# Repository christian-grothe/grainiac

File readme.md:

# Grainiac

Grainiac is a granular sampler. It currently runs as a vst3 plugin, standlone with a tui and a vst3 plugin with a tui style interface which is currently experimental and under development.

## Project Structure

| Crate                 | Description                                               |
| --------------------- | --------------------------------------------------------- |
| `grainiac_core`       | Core audio DSP engine (no UI dependencies)                |
| `grainiac_tui`        | Standalone JACK client with Ratatui TUI                   |
| `grainiac_plugin_tui` | VST3/CLAP plugin with Ratatui TUI editor _(experimental)_ |
| `grainiac_plugin_gui` | Vizia-based GUI plugin                                    |
| `midi_ctrl`           | PlatformIO firmware for Teensy 4.0 MIDI controller        |

## Config

You need a `config.json` file under `~/.config/grainiac/` with the following schema:

```json
{
  "presets": [
    {
      "gain": [0.5, 0.5, 0.5, 0.5],
      "loop_start": [0.25, 0.25, 0.25, 0.25],
      "loop_length": [0.5, 0.5, 0.5, 0.5],
      "density": [0.5, 0.5, 0.5, 0.5],
      "grain_length": [0.5, 0.5, 0.5, 0.5],
      "play_speed": [1.0, 1.0, 1.0, 1.0],
      "spray": [0.1, 0.1, 0.1, 0.1],
      "pan": [0.0, 0.0, 0.0, 0.0],
      "spread": [1.0, 1.0, 1.0, 1.0],
      "attack": [0.25, 0.25, 0.25, 0.25],
      "release": [0.25, 0.25, 0.25, 0.25],
      "pitch": [1, 1, 1, 1],
      "play_dir": [0, 0, 0, 0],
      "grain_dir": [0, 0, 0, 0],
      "mode": [0, 0, 0, 0],
      "name": "preset_1",
      "char": "1"
    }
  ],
  "mapping": {
    "loop_start": 40,
    "loop_length": 41,
    "density": 42,
    "grain_length": 43,
    "play_speed": 44,
    "spray": 45,
    "pan": 46,
    "spread": 47,
    "attack": 48,
    "release": 49,
    "pitch": 50,
    "gain": 51,
    "record": 52,
    "hold": 53,
    "play_dir": 54,
    "grain_dir": 55,
    "mode": 56
  }
}
```

The arrays under presets represent tracks A to D. The `char` field is the key to press to load the preset. The `name` field is currently unused.

The `mapping` section maps MIDI CC numbers to parameters. Each track corresponds to a MIDI channel (channel 1 = track A, channel 2 = track B, etc.).

To save and load audio files, manually create the folder `~/.local/share/grainiac/`.

## Key Mappings

| Key    | Function    |
| ------ | ----------- |
| `m`    | change mode |
| `0..9` | load / save |
| `n`    | switch view |
| `esc`  | close       |

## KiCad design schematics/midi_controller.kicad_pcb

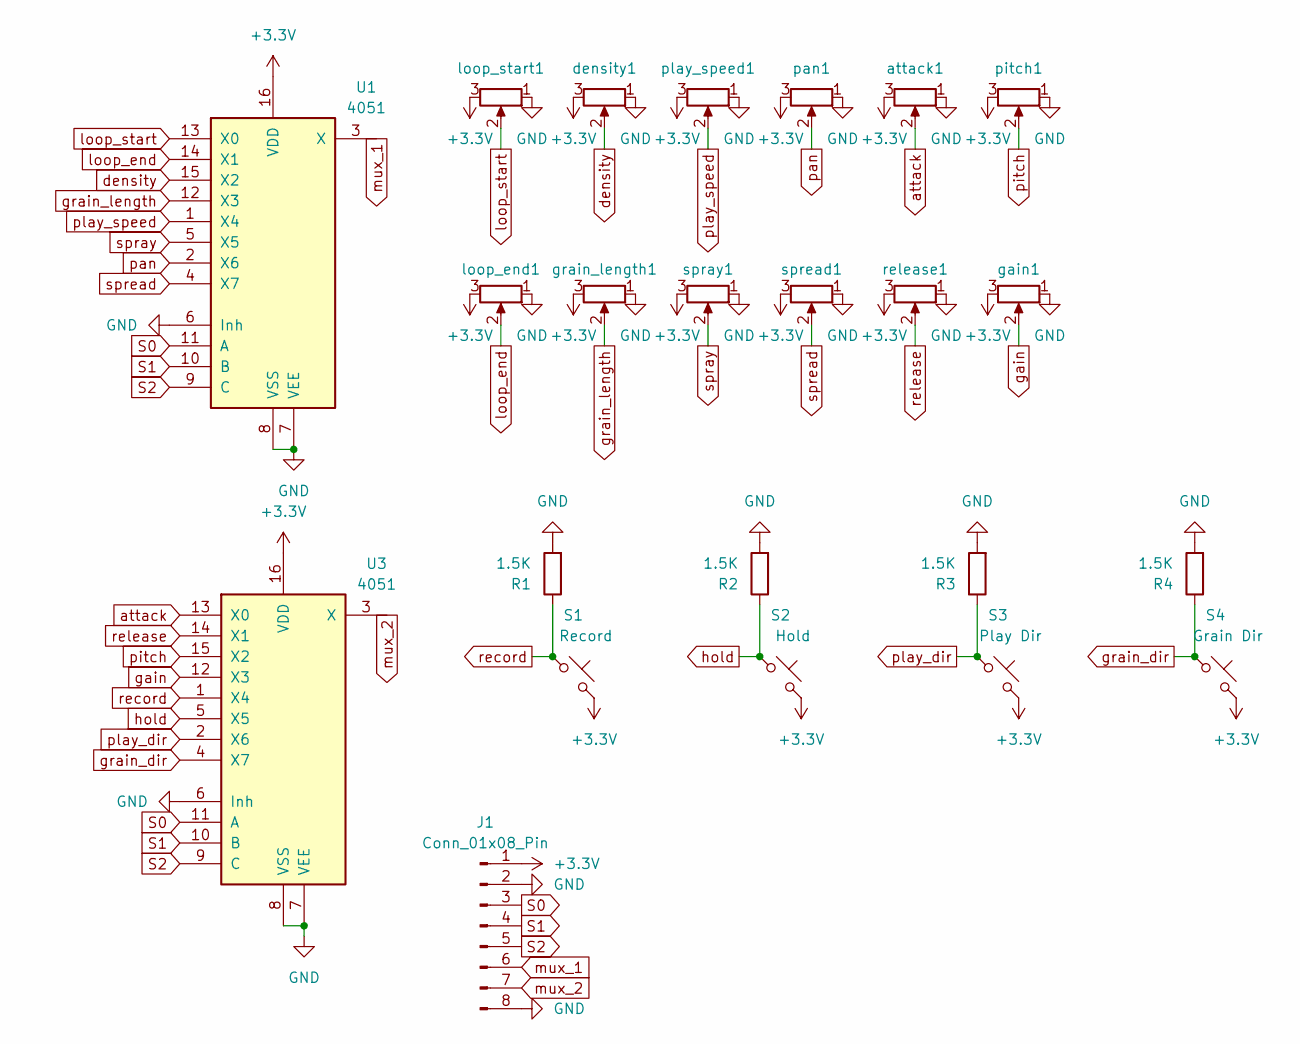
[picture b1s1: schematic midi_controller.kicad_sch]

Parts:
J1: Conn_01x08_Pin; IDC-Header_2x04_P2.54mm_Vertical
R1, R2, R3, R4: 1.5K; R_Axial_DIN0204_L3.6mm_D1.6mm_P5.08mm_Horizontal
S1: Record; SW_Cherry_MX_1.00u_PCB
S2: Hold; SW_Cherry_MX_1.00u_PCB
S3: Play Dir; SW_Cherry_MX_1.00u_PCB
S4: Grain Dir; SW_Cherry_MX_1.00u_PCB
U1, U3: 4051; DIP-16_W7.62mm_Socket
attack1: Potentiometer_TT_P0915N
density1: Potentiometer_TT_P0915N
gain1: Potentiometer_TT_P0915N
grain_length1: Potentiometer_TT_P0915N
loop_end1: Potentiometer_TT_P0915N
loop_start1: Potentiometer_TT_P0915N
pan1: Potentiometer_TT_P0915N
pitch1: Potentiometer_TT_P0915N
play_speed1: Potentiometer_TT_P0915N
release1: Potentiometer_TT_P0915N
spray1: Potentiometer_TT_P0915N
spread1: Potentiometer_TT_P0915N

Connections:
+3.3V: J1.1, S1.2, S2.2, S3.2, S4.2, U1.16 (VDD), U3.16 (VDD), attack1.3, density1.3, gain1.3, grain_length1.3, loop_end1.3, loop_start1.3, pan1.3, pitch1.3, play_speed1.3, release1.3, spray1.3, spread1.3
GND: J1.2, J1.8, R1.2, R2.2, R3.2, R4.2, U1.6 (Inh), U1.7 (VEE), U1.8 (VSS), U3.6 (Inh), U3.7 (VEE), U3.8 (VSS), attack1.1, density1.1, gain1.1, grain_length1.1, loop_end1.1, loop_start1.1, pan1.1, pitch1.1, play_speed1.1, release1.1, spray1.1, spread1.1
S0: J1.3, U1.11 (A), U3.11 (A)
S1: J1.4, U1.10 (B), U3.10 (B)
S2: J1.5, U1.9 (C), U3.9 (C)
attack: U3.13 (X0), attack1.2
density: U1.15 (X2), density1.2
gain: U3.12 (X3), gain1.2
grain_dir: R4.1, S4.1, U3.4 (X7)
grain_length: U1.12 (X3), grain_length1.2
hold: R2.1, S2.1, U3.5 (X5)
loop_end: U1.14 (X1), loop_end1.2
loop_start: U1.13 (X0), loop_start1.2
mux_1: J1.6, U1.3 (X)
mux_2: J1.7, U3.3 (X)
pan: U1.2 (X6), pan1.2
pitch: U3.15 (X2), pitch1.2
play_dir: R3.1, S3.1, U3.2 (X6)
play_speed: U1.1 (X4), play_speed1.2
record: R1.1, S1.1, U3.1 (X4)
release: U3.14 (X1), release1.2
spray: U1.5 (X5), spray1.2
spread: U1.4 (X7), spread1.2

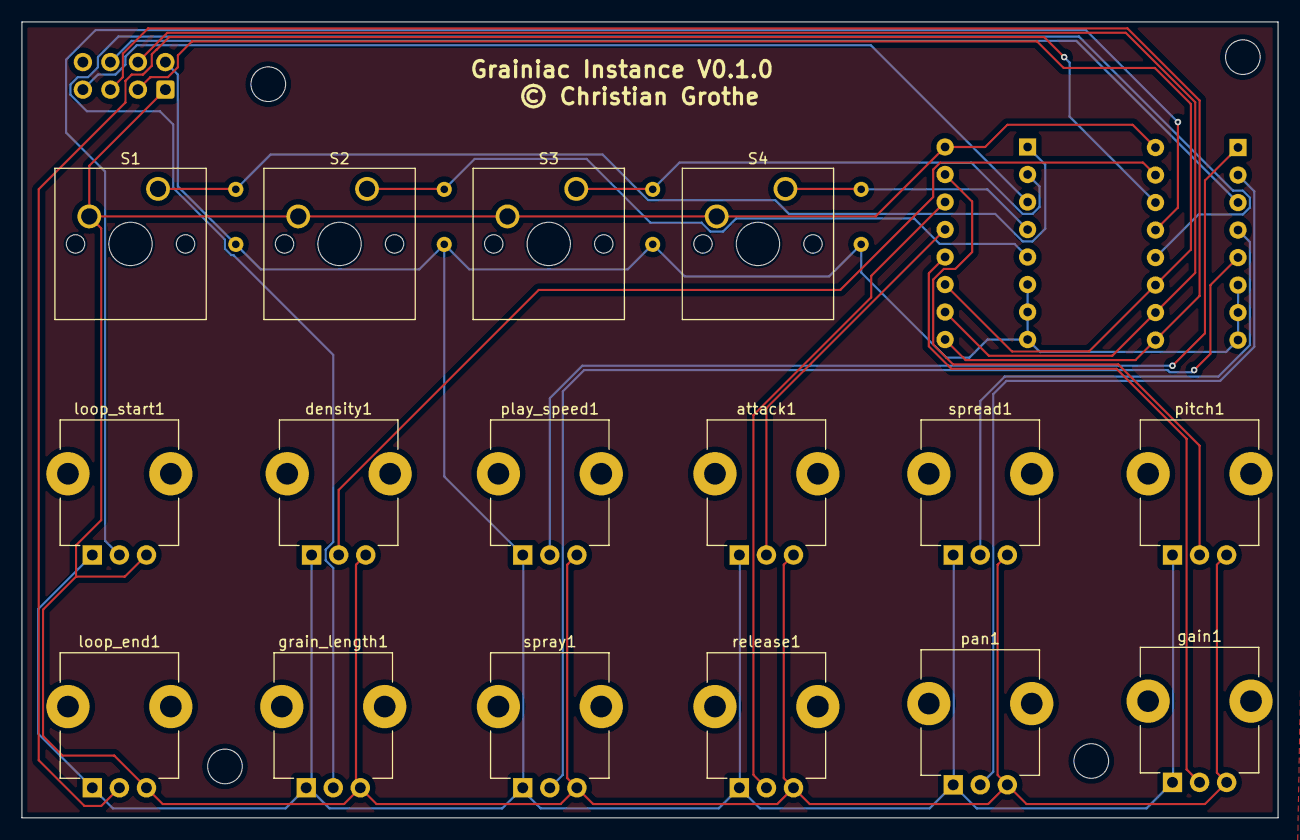
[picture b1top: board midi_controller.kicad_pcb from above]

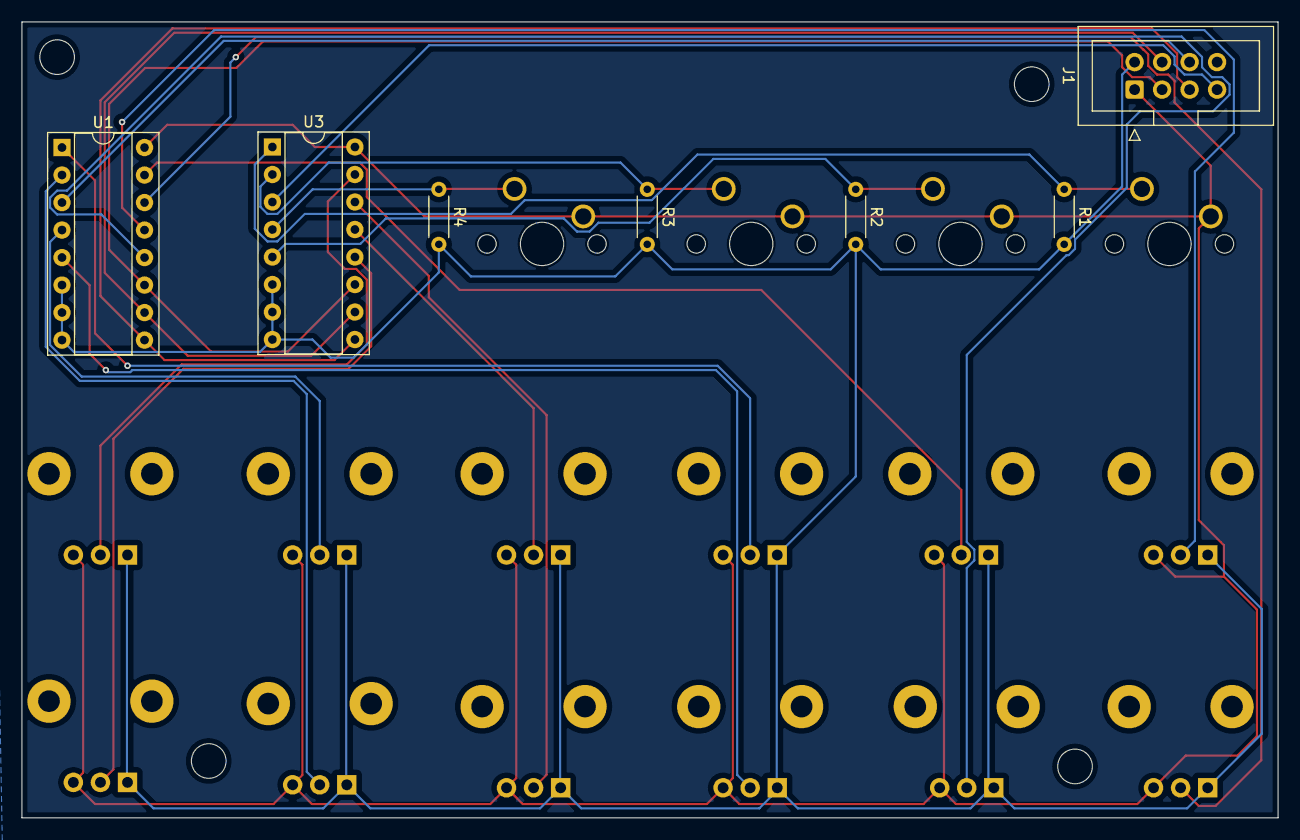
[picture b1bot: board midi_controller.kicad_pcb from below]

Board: 2 copper layers, 116.0 x 73.5 mm, 23 parts (7 on the bottom side), 23 nets.

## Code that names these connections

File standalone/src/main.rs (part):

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    let value = val as f32 / 126.0;

    match cc {
        x if x == mapping.loop_start => {
            sampler.set_loop_start(instance, value);
        }
        x if x == mapping.loop_length => {
            sampler.set_loop_length(instance, value);
        }
        x if x == mapping.density => {
            sampler.set_density(instance, value * 50.0);
        }
        x if x == mapping.grain_length => {
            sampler.set_grain_length(instance, value);
        }
        x if x == mapping.play_speed => {
            sampler.set_play_speed(instance, value * 2.0);
        }
        x if x == mapping.spray => {
            sampler.set_spray(instance, value);
        }
        x if x == mapping.pan => {
            sampler.set_pan(instance, (value * 2.0) - 1.0);
        }
        x if x == mapping.spread => {
            sampler.set_spread(instance, value);
        }
        x if x == mapping.attack => {
            sampler.set_attack(instance, value * 5.0);
        }
        x if x == mapping.release => {
            sampler.set_release(instance, value * 5.0);
        }
        x if x == mapping.pitch => {
            sampler.set_global_pitch(instance, (value * 24.0) as i8 - 12);
        }
        x if x == mapping.gain => {
            sampler.set_gain(instance, value);
        }
        x if x == mapping.record => {
            if value > 0.0 {
                sampler.record(instance);
            }
        }
        x if x == mapping.hold => {
            if value > 0.0 {
                sampler.toggle_hold(instance);
            }
        }
        x if x == mapping.play_dir => {
            if value > 0.0 {
                sampler.toggle_play_dir(instance);
            }
        }
        x if x == mapping.grain_dir => {
            if value > 0.0 {
                sampler.toggle_grain_dir(instance);
            }
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
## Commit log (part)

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2024-12-14 init commit
2024-12-19 triple buffer
2024-12-19 fixing event handling
2024-12-24 refactor
2024-12-24 instances
2024-12-25 typo fix
2024-12-26 loop start and length
2024-12-27 restructure repo
2024-12-27 license
2024-12-30 stereo pos
2025-01-01 jack
2025-01-01 removing prints
2025-01-04 custom tui widget
2025-01-07 midi mapping
2025-01-11 try rgb color
2025-01-11 bar num
2025-01-11 remove auto connect
2025-01-11 change layout
2025-01-11 change colors
2025-01-11 changing bar
2025-01-11 100 bars
2025-01-11 connect ports
2025-01-11 readme
2025-01-11 schematics
2025-01-21 fixing stuff
2025-01-21 fixes
2025-02-12 midi_ctrl
2025-02-16 auto connect midi device
2025-02-16 include script
2025-02-16 video readme
2025-03-20 parsing config
2025-03-24 parsing config
    parsing config
2025-03-25 state
2025-03-27 saving presets
2025-03-27 ui-refactor
2025-03-30 rtsan
    rtsan
2025-03-30 refactor tests
2025-04-05 small fixes
2025-04-24 loading samples
2025-04-24 naive audio storing
2025-05-19 fix: disable the kitty keyboard protocol on exit
2025-07-08 input and output peak
2025-07-12 restructure
2025-07-12 preset view
2025-07-13 remove draft
2025-07-16 tape mode
2025-07-16 change config
2025-07-18 remove plugin
2025-07-18 reorder stuff
2025-07-18 working plugin
2025-07-18 adding old plugin
2025-07-18 plugin init commit
2025-07-18 fix waveform
2025-07-20 gitignore
2025-07-22 dial and select
    dial and select
2025-07-23 style
2025-07-24 naive audio loading
2025-07-26 audio import
2025-07-26 refactor dial
2025-07-27 refactor play_heads
2025-07-27 stuff
2025-07-29 adding font
2025-07-29 font
2026-02-20 select audio source
2026-02-20 attempt to fix audio loading
2026-02-20 another attempt to fix audio loading
2026-02-20 renaming stuff and adding grainiac_plugin_tui
2026-02-21 variable instance num
2026-02-24 adding fader widget
2026-02-24 adding grainiac_plugin_tui
2026-02-24 refactor readme
2026-03-24 adding ci
2026-03-24 fix ci
2026-03-28 compile all
2026-03-29 no testing in ci
2026-04-07 Polish plugin GUI for clearer layering
2026-04-07 Enable dragging loop region in waveform
2026-04-07 add back-and-forth play direction for GUI controls
2026-04-07 fix back-and-forth direction getting stuck
2026-04-28 run `cargo clippy --fix` in all crates
2026-06-18 new ui

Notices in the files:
schematics/midi_controller.kicad_pcb:
© Christian Grothe
